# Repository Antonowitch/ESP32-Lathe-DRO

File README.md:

# ESP32 Lathe DRO – Digital Readout for up to 4 Axes

**English** | [Deutsch](README.de.md)

A digital readout (DRO) for the lathe, built around an **ESP32 DevKit V1**. It reads up to four
linear scales (glass scales or magnetic tape) and shows the positions on **any touch device** –
phone or tablet – through a web page served by the ESP32's own Wi-Fi access point. No app, no
internet connection, no display hardware needed.

🎥 **Video (German, English subtitles):** [https://www.youtube.com/watch?v=9dQxbsSbBd4](https://www.youtube.com/watch?v=9dQxbsSbBd4)

🛠️ **Building and printing the case (German):** [https://www.youtube.com/watch?v=JSoUT4cyio0](https://www.youtube.com/watch?v=JSoUT4cyio0)

📺 Channel: [Anton CNC on YouTube](https://www.youtube.com/@boessi)

Firmware version: **v1.0**

---

## Contents

- [Features](#features)
- [What's in this repository](#whats-in-this-repository)
- [Hardware](#hardware)
- [Wiring](#wiring)
- [Flashing the firmware (no Arduino IDE needed)](#flashing-the-firmware-no-arduino-ide-needed)
- [First start](#first-start)
- [Operation](#operation)
- [How it works](#how-it-works)
- [Building the firmware yourself](#building-the-firmware-yourself)
- [Testing for lost steps](#testing-for-lost-steps)
- [License and disclaimer](#license-and-disclaimer)

---

## Features

- **2, 3 or 4 axes** (X, Z, U, W), selectable in the settings
- **Hardware counting:** the ESP32's pulse counter (PCNT) decodes the A/B quadrature signals in
  silicon, 4× evaluation of every edge – no lost steps from busy software, 0 % CPU load for counting
- Default **200 pulses/mm (5 µm scales)**, presets for 1 µm, any custom value per axis
- **10 tools (T1–T10)** with their own offsets; T1 is the master/reference tool
- **ABS / INC per axis** – e.g. Z in chain-dimension mode while X stays absolute
- **Radius / diameter** mode for the cross slide
- **Compound slide helper** for taper and thread turning (angle → ΔX / ΔZ)
- **mm or inch** display
- **SAVE** stores offsets, active tool and scale positions permanently (NVS flash)
- **Connection indicator:** green/red dot, "CONNECTION LOST" banner, warning tone
- Responsive web UI for phones (portrait) and iPads; can be installed as a home-screen app

> The long-press buttons (SAVE, settings gear, 2X/3X/4X, axis direction) are made for touch
> screens. Use a phone or tablet – a mouse cannot do the long press.

*Main display: iPad in landscape. Below: the same interface on a phone.*

---

## What's in this repository

| Folder | Content |
|---|---|
| [`firmware/ESP32_Lathe_DRO/`](firmware/ESP32_Lathe_DRO/) | Arduino source code (`.ino`) |
| [`firmware/bin/`](firmware/bin/) | Ready-to-flash binaries (see [Flashing](#flashing-the-firmware-no-arduino-ide-needed)) |
| [`hardware/kicad/`](hardware/kicad/) | **Recommended PCB** – KiCad 10 project and [schematic as PDF](hardware/kicad/DRO_schematic.pdf) |
| [`hardware/kicad/fabrication/`](hardware/kicad/fabrication/) | Gerber, BOM and pick-and-place files for JLCPCB, [ordering notes](hardware/kicad/fabrication/ORDERING.md) |
| [`hardware/fusion-legacy/`](hardware/fusion-legacy/) | First PCB version from Fusion – **without pull-up resistors and without the on/off switch terminal**, see its [README](hardware/fusion-legacy/README.md) |
| [`case/`](case/) | Case: Fusion design [`DRO_Gehaeuse.f3d`](case/DRO_Gehaeuse.f3d) (housing, lid, aluminium plate, PCB model, CAM setup) and 3D-print files (STL and 3MF) |
| [`docs/diagram/`](docs/diagram/) | System diagram (Excalidraw source and SVG) |
| [`images/`](images/) | Photos and renderings |

---

## Hardware

### Parts

- **PCB** from [`hardware/kicad/`](hardware/kicad/), 130 × 80 mm, 2 layers. JLCPCB can assemble the
  SMD parts on the bottom side (U1, U2, R1–R8, C1, C2); everything else is through-hole and easy to
  solder by hand. Details and part numbers: [ORDERING.md](hardware/kicad/fabrication/ORDERING.md).
- **ESP32 DevKit V1, 30 pins** (ESP32-WROOM-32). The antenna points outward over the board edge.
- **Linear scales** with 5 V TTL quadrature output (A/B), e.g. glass scales or magnetic tape
  readers, up to four.
- **5 V power supply** with a **5.5 × 2.1 mm barrel plug, center positive** (≥ 2 A recommended) and an **on/off switch** for the case.
  I use a Mean Well GST18A05-P1J (5 V, 3 A). A 5.5 × 2.5 mm plug is too loose on the jack (2.0 mm center pin).
- **Sub-D 9 (DB9) panel connectors** for the scales, cables to the JST-XH sockets on the PCB.
- **Case:** [`case/Gehaeuse.stl`](case/Gehaeuse.stl) and [`case/Deckel.stl`](case/Deckel.stl)
  (also as 3MF); the editable Fusion design is [`case/DRO_Gehaeuse.f3d`](case/DRO_Gehaeuse.f3d).
  How the case is built and printed: [video](https://www.youtube.com/watch?v=JSoUT4cyio0).

### The PCB in short

- **J1 / J2 / J3 / J5** (JST-XH, 5 pins): scale inputs X / Z / U / W
- **R1–R8** (10 kΩ to +5 V): pull-ups on every A/B line, so an unplugged input does not float
  and produce phantom counts
- **U1, U2** (SN74LVC14A): Schmitt-trigger inverters at 3.3 V with 5 V tolerant inputs – they turn
  slow, noisy edges into clean square waves and shift 5 V down to 3.3 V for the ESP32. The
  inversion does no harm because both tracks are inverted alike.
- **J4** barrel jack 5 V → **J10** on/off switch → +5 V → ESP32 VIN
- **J6–J9** screw terminals: spare GPIOs, +5 V, +3.3 V and GND for future extensions

*Schematic – click for the PDF.*

---

## Wiring

### Scale → Sub-D 9 (as wired in the case)

| Sub-D pin | Signal |
|---|---|
| 2 | GND |
| 4 | GND (shield) |
| 6 | Channel A |
| 7 | +5 V supply for the scale |
| 8 | Channel B |

Pinouts of scales differ between manufacturers – **always check your scale's datasheet** and
measure before connecting. Swapping A and B only inverts the counting direction (which can also be
changed in the settings).

### Sub-D → JST-XH on the PCB

| JST pin | 1 | 2 | 3 | 4 | 5 |
|---|---|---|---|---|---|
| Signal | B | GND | +5 V | GND | A |

The same wiring for all four sockets (J1, J2, J3, J5). The D-sub numbers are mirrored on the solder
side – most sockets have them embossed next to the solder cups.

### Axes → ESP32 inputs

| Axis | Socket | Channel A | Channel B |
|---|---|---|---|
| X | J1 | GPIO 32 | GPIO 33 |
| Z | J2 | GPIO 25 | GPIO 26 |
| U | J3 | GPIO 27 | GPIO 14 |
| W | J5 | GPIO 19 | GPIO 18 |

### Spare terminals

| Terminal | Pins |
|---|---|
| J6 | GPIO 23, GND, +5 V |
| J7 | GPIO 4, GPIO 17, GPIO 5 |
| J8 | +3.3 V, GND, GPIO 21, GPIO 22 |
| J9 | +5 V, +3.3 V, GND, GND |
| J10 | on/off switch (between barrel jack and +5 V) |

---

## Flashing the firmware (no Arduino IDE needed)

You need a Windows PC, a USB cable (data, not charge-only) and the ESP32 DevKit.

### 1. Download the tools

- **Flash Download Tool** from Espressif:
  [espressif.com → Support → Download → Other Tools → "Flash Download Tools"](https://www.espressif.com/en/support/download/other-tools)
  ([user guide](https://docs.espressif.com/projects/esp-test-tools/en/latest/esp32/production_stage/tools/flash_download_tool.html)).
  Unzip it and start `flash_download_tool_*.exe` – no installation needed.
- **USB driver**, if Windows shows no COM port for the board. Look at the small chip next to the
  USB socket:
  - CP2102 / CP210x → [Silicon Labs CP210x VCP driver](https://www.silabs.com/developer-tools/usb-to-uart-bridge-vcp-drivers)
  - CH340 → [WCH CH341SER driver](https://www.wch.cn/downloads/CH341SER_EXE.html)
- **The firmware:** [`firmware/bin/ESP32_Lathe_DRO_v1.0_merged.bin`](firmware/bin/ESP32_Lathe_DRO_v1.0_merged.bin)
  (on GitHub: open the file, then "Download raw file").

### 2. Flash

1. **Disconnect the 5 V power supply** of the DRO and connect the ESP32 to the PC by USB.
   In the Device Manager, note the COM port (e.g. COM3).
2. Start the Flash Download Tool. In the first dialog choose
   **ChipType: ESP32, WorkMode: Develop, LoadMode: UART** → OK.
3. Set everything as in the picture below:
   1. First line of the **SPIDownload** tab: tick the box, select
      `ESP32_Lathe_DRO_v1.0_merged.bin` with "…" and enter the address **`0x0`**.
      All other lines stay unticked.
   2. **SPI SPEED: 40MHz, SPI MODE: DIO**, leave "DoNotChgBin" ticked.
   3. Select the **COM port**, **BAUD: 921600** (if it fails: 115200).
   4. For the very first flash, click **ERASE** once and wait for "FINISH". This clears the whole
      flash, including previously saved settings.
   5. Click **START** and wait until the panel shows **"FINISH"**.
4. Press **EN** on the ESP32 (or unplug and replug USB) to restart it. Done.

<details>
<summary>Alternative: four single files instead of the merged file</summary>

| File | Address |
|---|---|
| `bootloader.bin` | `0x1000` |
| `partitions.bin` | `0x8000` |
| `boot_app0.bin` | `0xe000` |
| `ESP32_Lathe_DRO_v1.0_app.bin` | `0x10000` |

</details>

<details>
<summary>Alternative for Linux / macOS: esptool</summary>

```
pip install esptool
esptool.py --chip esp32 --port /dev/ttyUSB0 write_flash 0x0 ESP32_Lathe_DRO_v1.0_merged.bin
```

</details>

---

## First start

1. Switch the DRO on and connect your phone or tablet to the Wi-Fi network
   **`AntonCNC_ESP32-DRO`**, password **`12345678`**.
   It is a good idea to change the password: it is set in the source code (`password` near the
   top of the `.ino`), so this requires building the firmware yourself.
2. Open **http://192.168.4.1** in Chrome (Android) or Safari (iPad). Portrait orientation works
   best on phones.
3. Install it as an app: browser menu → **"Add to Home screen" / "Install app"**. Then start the
   DRO from the new icon – it opens full-screen without browser bars.
4. Keep the screen awake: set the display timeout to the maximum (or Android developer options →
   "Stay awake" while charging). Optional: Android "App pinning" or iPadOS "Guided Access".
5. Open the settings (**press and hold the gear ⚙ for 0.8 s**) and set
   the number of axes, the counting direction of each axis and the scale resolution.

---

## Operation

| Action | How |
|---|---|
| Select tool | Tap **T1 … T10** in the bottom bar. T1 is the reference tool: in ABS mode all other tools are stored relative to T1 – touch off T1 again after a reboot. |
| Zero an axis | Red **Z** next to the axis → confirm with **YES** (only for the active tool) |
| Enter a value | Orange **I** → numpad (with +/-) → **SET** |
| ABS / INC | Tap the **axis letter**: green = ABS, yellow = INC, per axis |
| Radius / diameter | **R / D** on the X row – D shows the diameter (×2) |
| Compound slide helper | **∠** on the U row – angle, raw U, resulting ΔX/ΔZ and combined X/Z. Not saved (resets on reload). |
| Save | Press and hold **SAVE** for about 1 s until the tone – stores offsets, active tool, ABS/INC state and the scale positions |
| Settings | Press and hold **⚙** for 0.8 s: mm/inch, number of axes (hold 1 s), axis direction (hold 0.8 s), scale resolution (5 µm / 1 µm / custom, **SAVE RESOLUTIONS**) |
| Connection lost | Red dot and banner "CONNECTION LOST" → tap the banner to reload. There is intentionally no silent auto-reconnect. |

---

## How it works

- **Why an ESP32?** A 5 µm scale gives 200 counts per mm – at 50 mm/s that is 10,000 counts per
  second per axis. An Arduino Uno has only two interrupt pins (eight would be needed) and no Wi-Fi;
  an ESP8266 has one core and no hardware counter. The ESP32 has **hardware pulse counters (PCNT)**
  and **two cores**.
- **Core 1** runs the math: it reads the counters, applies tool offsets, diameter mode etc. and
  writes the positions into shared memory, protected by a mutex.
- **Core 0** runs the Wi-Fi access point, the web server and the WebSocket that sends the positions
  to the browser (max. 20 Hz, only on change, plus a heartbeat every second for the connection
  indicator).
- The PCNT counters are 16 bit. At ±30,000 counts (= 150 mm at 5 µm) a high-priority interrupt
  moves the count into a 32-bit total – the range is practically unlimited.
- A hardware glitch filter ignores pulses shorter than 1.25 µs.
- Scale resolution, direction, unit and number of axes are stored in NVS flash.

The diagram source can be opened and edited on [excalidraw.com](https://excalidraw.com)
([`docs/diagram/ESP32_Dual_Core_Diagramm.excalidraw`](docs/diagram/ESP32_Dual_Core_Diagramm.excalidraw)).

---

## Building the firmware yourself

Use **exactly these versions** – the Arduino IDE (2.x) is fine:

| Component | Version |
|---|---|
| Board package **esp32 by Espressif Systems** | **2.0.14** – do **not** use 3.x: it removes the legacy PCNT driver used here and makes AsyncTCP unstable |
| [AsyncTCP](https://github.com/dvarrel/AsyncTCP) | 1.1.4 |
| [ESPAsyncWebServer](https://github.com/lacamera/ESPAsyncWebServer) | 3.1.0 |

Board: **ESP32 Dev Module**, flash 4 MB, partition scheme "Default 4MB with spiffs".
Open [`firmware/ESP32_Lathe_DRO/ESP32_Lathe_DRO.ino`](firmware/ESP32_Lathe_DRO/ESP32_Lathe_DRO.ino),
compile and upload. The header of the `.ino` contains the full technical documentation.

---

## Testing for lost steps

Move the axis against a fixed stop or gauge block and zero it. Then crank the axis quickly more
than 200 mm away (this triggers a counter overflow at 150 mm) and back to the same stop. The
display must show 0.00 again.

---

## License and disclaimer

- Firmware (`firmware/`): [MIT License](LICENSE)
- Hardware, case, diagram and images (`hardware/`, `case/`, `docs/`, `images/`):
  [CC BY-SA 4.0](LICENSE-hardware)

This project is provided "as is", without any warranty. The author is not liable for any damage,
malfunction or other consequences of its use. It is meant for hobby and experimental use on machine
tools – observe proper safety precautions, and verify wiring, signal levels and machine operation
yourself at all times.

Made by **Anton CNC** – [YouTube](https://www.youtube.com/@boessi)

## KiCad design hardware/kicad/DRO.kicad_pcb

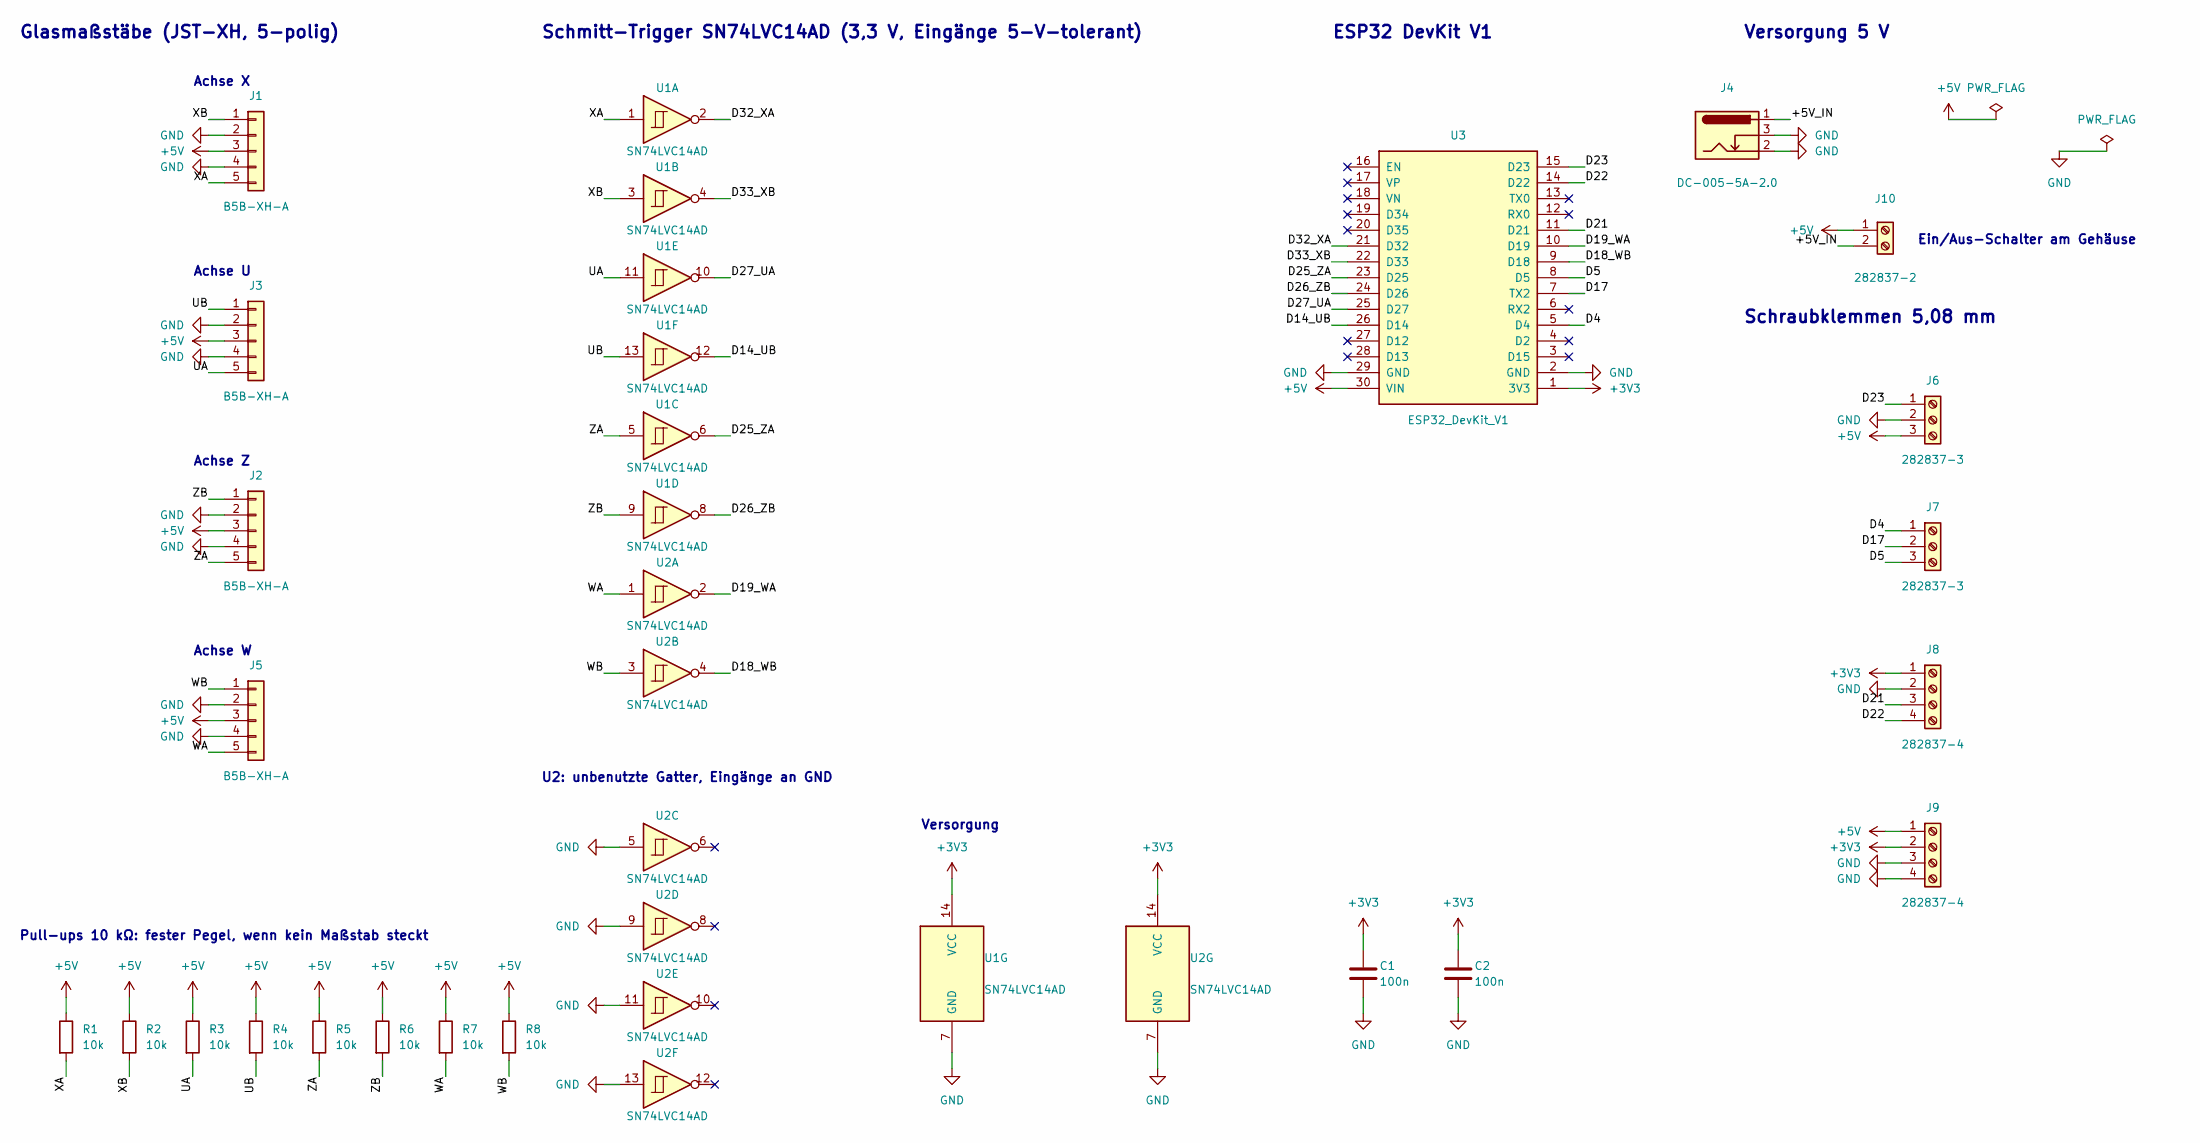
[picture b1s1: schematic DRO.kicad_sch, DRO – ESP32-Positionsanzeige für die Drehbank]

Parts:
C1, C2: 100n; C_0805_2012Metric_Pad1.18x1.45mm_HandSolder; MPN CC0805KRX7R9BB104; LCSC C49678
J1, J2, J3, J5: B5B-XH-A; JST_XH_B5B-XH-A_1x05_P2.50mm_Vertical; MPN B5B-XH-A(LF)(SN); LCSC C157991
J4: DC-005-5A-2.0; BarrelJack_Horizontal; MPN DC-005-5A-2.0; LCSC C381116
J6, J7: 282837-3; TerminalBlock_TE_282837-3_P5.08mm; MPN 282837-3; LCSC C589616
J8, J9: 282837-4; TerminalBlock_TE_282837-4_P5.08mm; MPN 282837-4; LCSC C5172818
J10: 282837-2; TerminalBlock_TE_282837-2_P5.08mm; MPN 282837-2; LCSC C592976
R1, R2, R3, R4, R5, R6, R7, R8: 10k; R_0805_2012Metric_Pad1.20x1.40mm_HandSolder; MPN 0805W8F1002T5E; LCSC C17414
U1, U2: SN74LVC14AD; SOIC-14_3.9x8.7mm_P1.27mm; MPN SN74LVC14ADR; LCSC C133541
U3: ESP32_DevKit_V1; ESP32_DevKit_V1_30Pin

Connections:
+3V3: C1.1, C2.1, J8.1, J9.2, U1.14 (VCC), U2.14 (VCC), U3.1 (3V3)
+5V: J1.3, J2.3, J3.3, J5.3, J6.3, J9.1, J10.1, R1.1, R2.1, R3.1, R4.1, R5.1, R6.1, R7.1, R8.1, U3.30 (VIN)
/+5V_IN: J4.1, J10.2
/D4: J7.1, U3.5 (D4)
/D5: J7.3, U3.8 (D5)
/D14_UB: U1.12, U3.26 (D14)
/D17: J7.2, U3.7 (TX2)
/D18_WB: U2.4, U3.9 (D18)
/D19_WA: U2.2, U3.10 (D19)
/D21: J8.3, U3.11 (D21)
/D22: J8.4, U3.14 (D22)
/D23: J6.1, U3.15 (D23)
/D25_ZA: U1.6, U3.23 (D25)
/D26_ZB: U1.8, U3.24 (D26)
/D27_UA: U1.10, U3.25 (D27)
/D32_XA: U1.2, U3.21 (D32)
/D33_XB: U1.4, U3.22 (D33)
/UA: J3.5, R3.2, U1.11
/UB: J3.1, R4.2, U1.13
/WA: J5.5, R7.2, U2.1
/WB: J5.1, R8.2, U2.3
/XA: J1.5, R1.2, U1.1
/XB: J1.1, R2.2, U1.3
/ZA: J2.5, R5.2, U1.5
/ZB: J2.1, R6.2, U1.9
GND: C1.2, C2.2, J1.2, J1.4, J2.2, J2.4, J3.2, J3.4, J4.2, J4.3, J5.2, J5.4, J6.2, J8.2, J9.3, J9.4, U1.7 (GND), U2.5, U2.7 (GND), U2.9, U2.11, U2.13, U3.2 (GND), U3.29 (GND)

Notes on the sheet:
U2: unbenutzte Gatter, Eingänge an GND
Achse Z
Schmitt-Trigger SN74LVC14AD (3,3 V, Eingänge 5-V-tolerant)
Schraubklemmen 5,08 mm
Achse U
Achse W
Glasmaßstäbe (JST-XH, 5-polig)
ESP32 DevKit V1
Achse X
Versorgung
Versorgung 5 V
Pull-ups 10 kΩ: fester Pegel, wenn kein Maßstab steckt
Ein/Aus-Schalter am Gehäuse

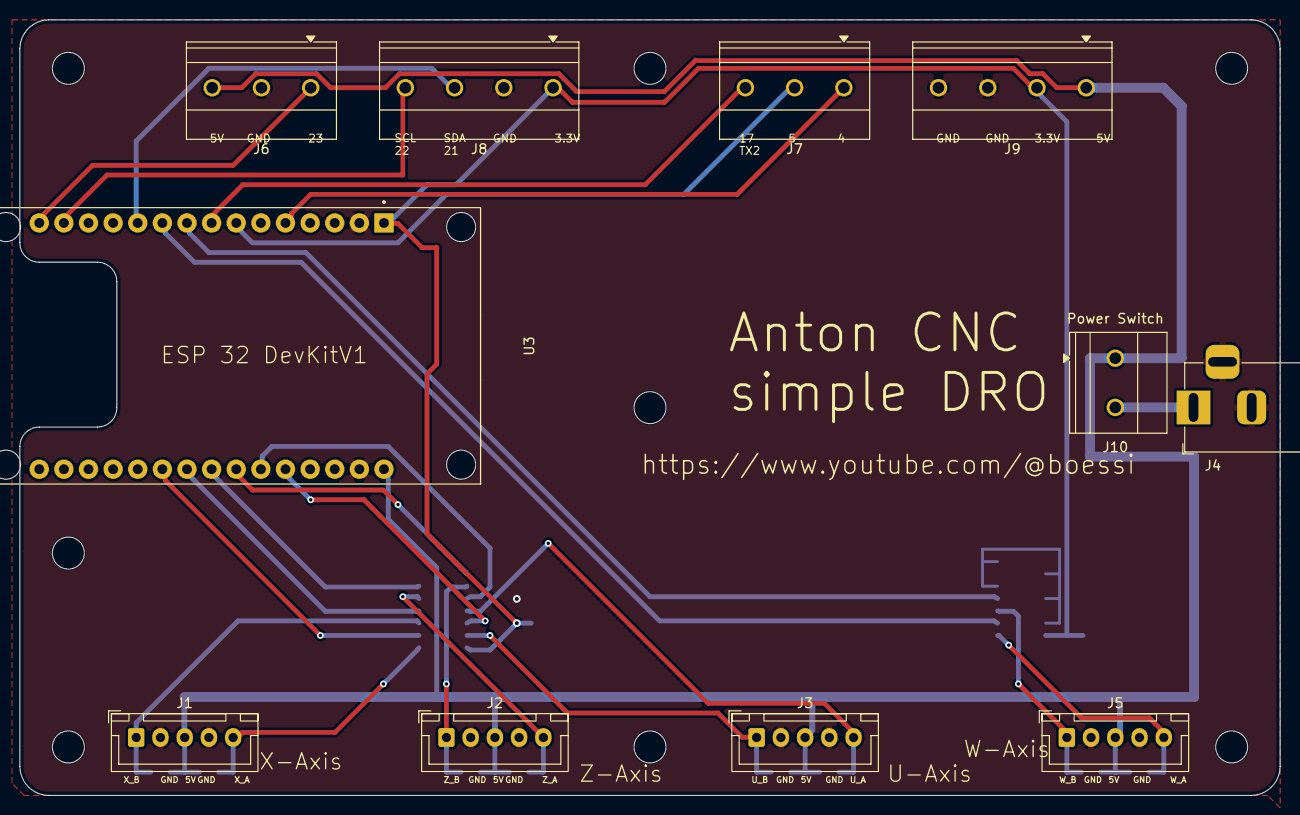
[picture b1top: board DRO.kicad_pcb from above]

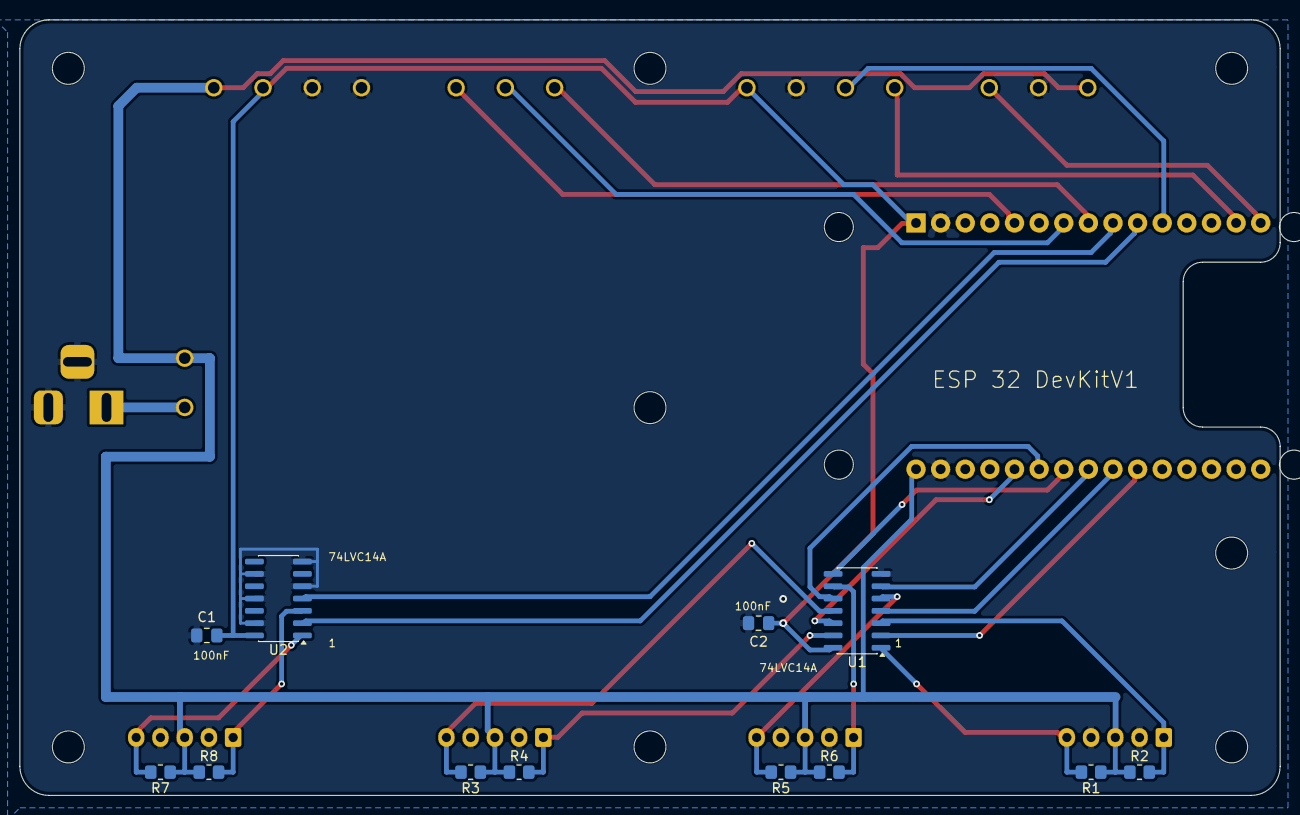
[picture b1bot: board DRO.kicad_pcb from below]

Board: 2 copper layers, 130.0 x 80.0 mm, 31 parts (12 on the bottom side), 26 nets.

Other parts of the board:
H1, H2, H3, H4, H5, H6, H7, H8: MountingHole_3.3mm
